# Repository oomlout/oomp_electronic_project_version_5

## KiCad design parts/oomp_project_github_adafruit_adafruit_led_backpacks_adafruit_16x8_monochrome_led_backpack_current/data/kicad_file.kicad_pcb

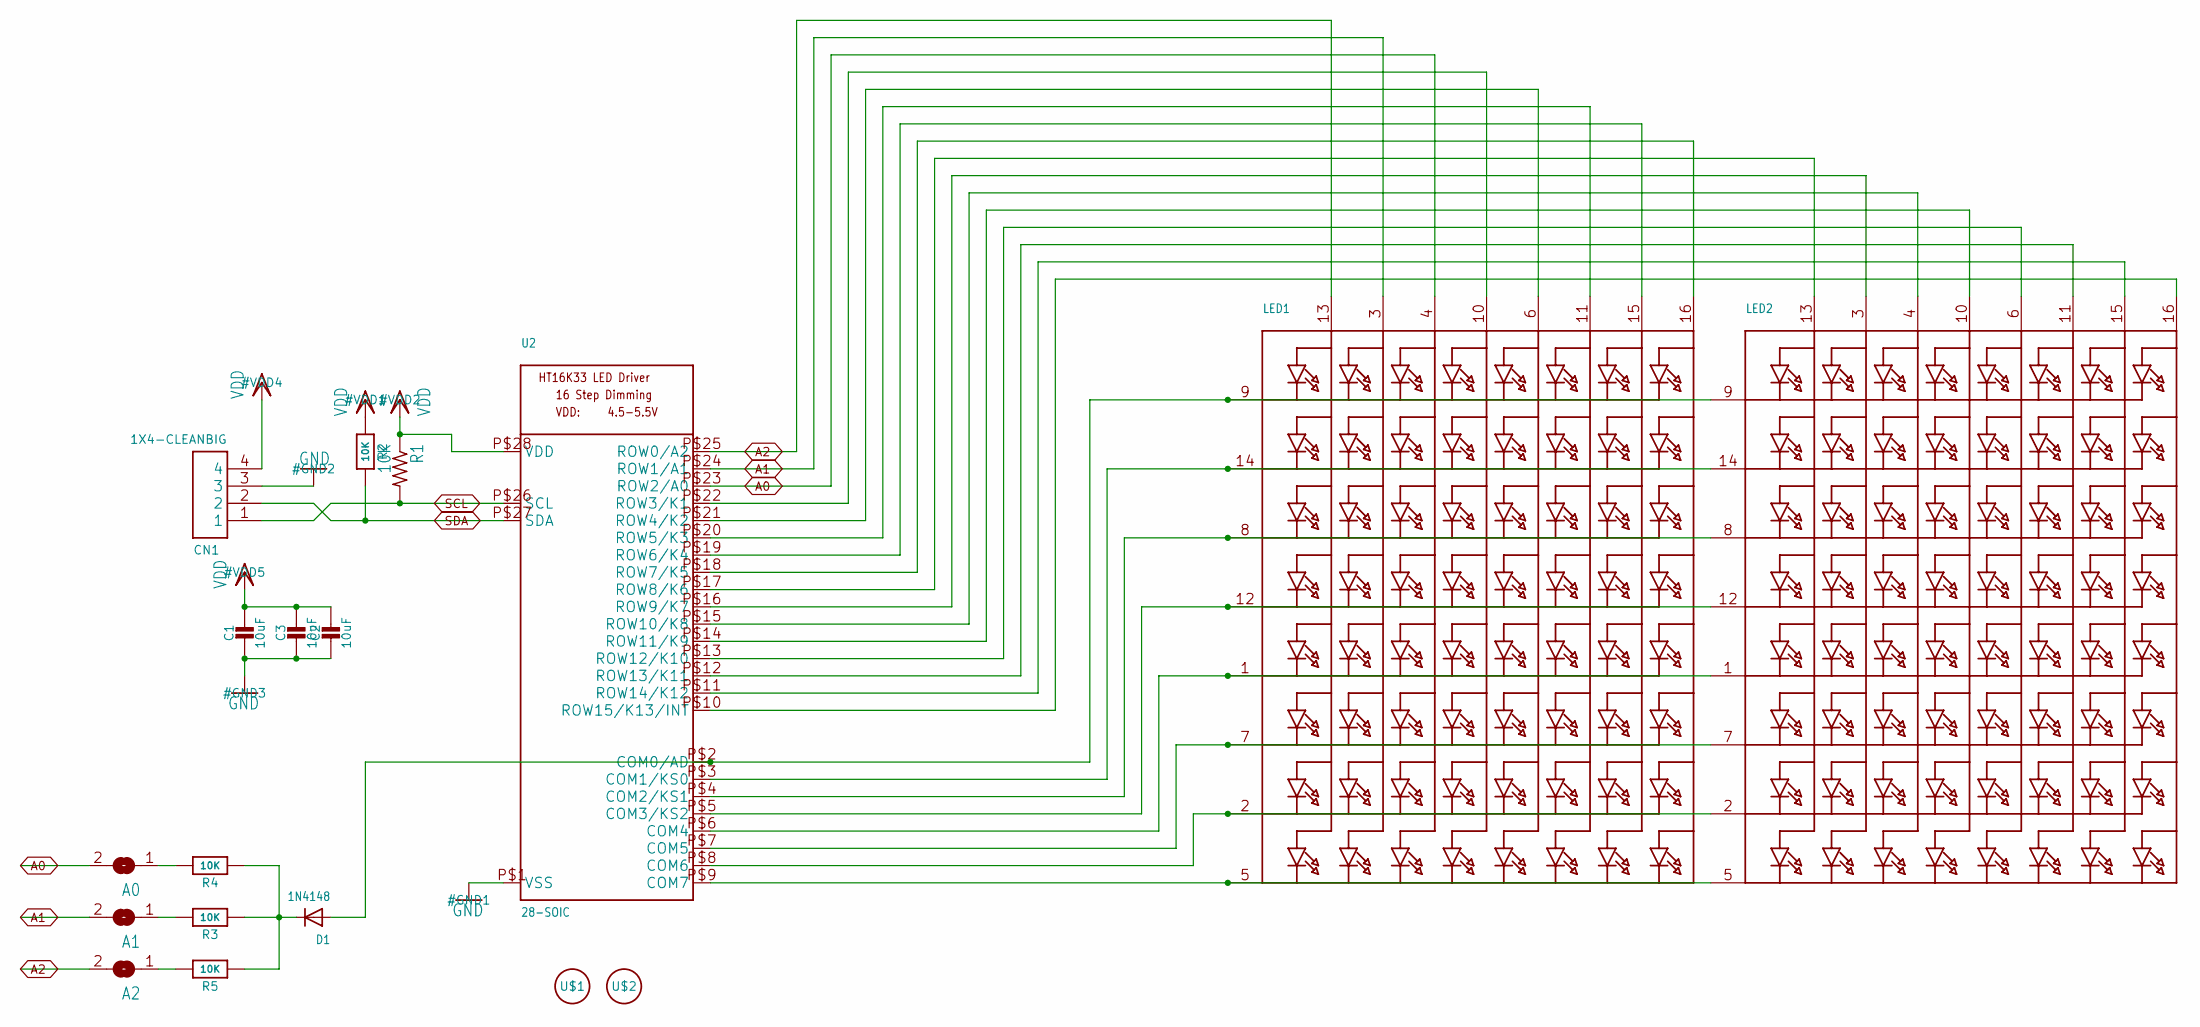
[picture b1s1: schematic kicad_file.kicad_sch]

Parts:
A0, A1, A2: SOLDERJUMPERREFLOW_NOPASTE; SOLDERJUMPER_REFLOW_NOPASTE
C1, C2, C3: 10uF; 0805-NO
CN1: 1X4-CLEANBIG; 1X04-CLEANBIG
D1: 1N4148; SOD-323F
LED1, LED2: DISP_SEGMENT_8X8_ROWCATHODEM12A881UR; SEGMENT_BL-M12A881UR
R1: 10K; R0805
R2, R3, R4, R5: 10K; 0805-NO
U2: 28-SOIC; SOP28_300MIL
U$1, U$2: FIDUCIAL; FIDUCIAL_1MM

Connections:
A0: A0.2, LED1.4 (A3), U2.P$23 (ROW2/A0)
A1: A1.2, LED1.3 (A2), U2.P$24 (ROW1/A1)
A2: A2.2, LED1.13 (A1), U2.P$25 (ROW0/A2)
GND: C1.2, C2.2, C3.2, CN1.3, U2.P$1 (VSS)
unnamed: LED1.5 (K8), LED2.5 (K8), U2.P$9 (COM7)
unnamed: LED1.2 (K7), LED2.2 (K7), U2.P$8 (COM6)
unnamed: LED1.7 (K6), LED2.7 (K6), U2.P$7 (COM5)
unnamed: LED1.1 (K5), LED2.1 (K5), U2.P$6 (COM4)
unnamed: LED1.12 (K4), LED2.12 (K4), U2.P$5 (COM3/KS2)
unnamed: LED1.8 (K3), LED2.8 (K3), U2.P$4 (COM2/KS1)
unnamed: LED1.14 (K2), LED2.14 (K2), U2.P$3 (COM1/KS0)
unnamed: D1.A, LED1.9 (K1), LED2.9 (K1), U2.P$2 (COM0/AD)
unnamed: A2.1, R5.2
unnamed: LED2.15 (A7), U2.P$11 (ROW14/K12)
unnamed: LED2.11 (A6), U2.P$12 (ROW13/K11)
unnamed: LED2.16 (A8), U2.P$10 (ROW15/K13/INT)
unnamed: D1.C, R3.1, R4.1, R5.1
unnamed: A1.1, R3.2
unnamed: A0.1, R4.2
unnamed: LED1.16 (A8), U2.P$18 (ROW7/K5)
unnamed: LED1.15 (A7), U2.P$19 (ROW6/K4)
unnamed: LED1.6 (A5), U2.P$21 (ROW4/K2)
unnamed: LED1.10 (A4), U2.P$22 (ROW3/K1)
unnamed: LED1.11 (A6), U2.P$20 (ROW5/K3)
unnamed: LED2.13 (A1), U2.P$17 (ROW8/K6)
unnamed: LED2.3 (A2), U2.P$16 (ROW9/K7)
unnamed: LED2.10 (A4), U2.P$14 (ROW11/K9)
unnamed: LED2.4 (A3), U2.P$15 (ROW10/K8)
unnamed: LED2.6 (A5), U2.P$13 (ROW12/K10)
SCL: CN1.1, R1.2, U2.P$26 (SCL)
SDA: CN1.2, R2.2, U2.P$27 (SDA)
VDD: C1.1, C2.1, C3.1, CN1.4, R1.1, R2.1, U2.P$28 (VDD)

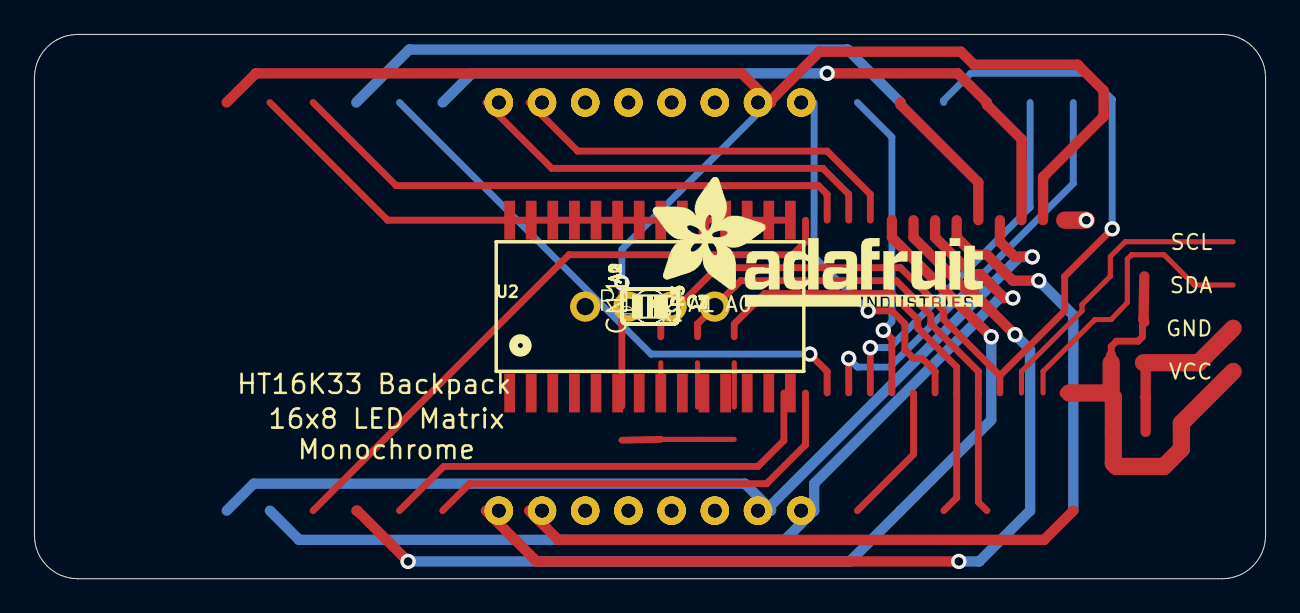
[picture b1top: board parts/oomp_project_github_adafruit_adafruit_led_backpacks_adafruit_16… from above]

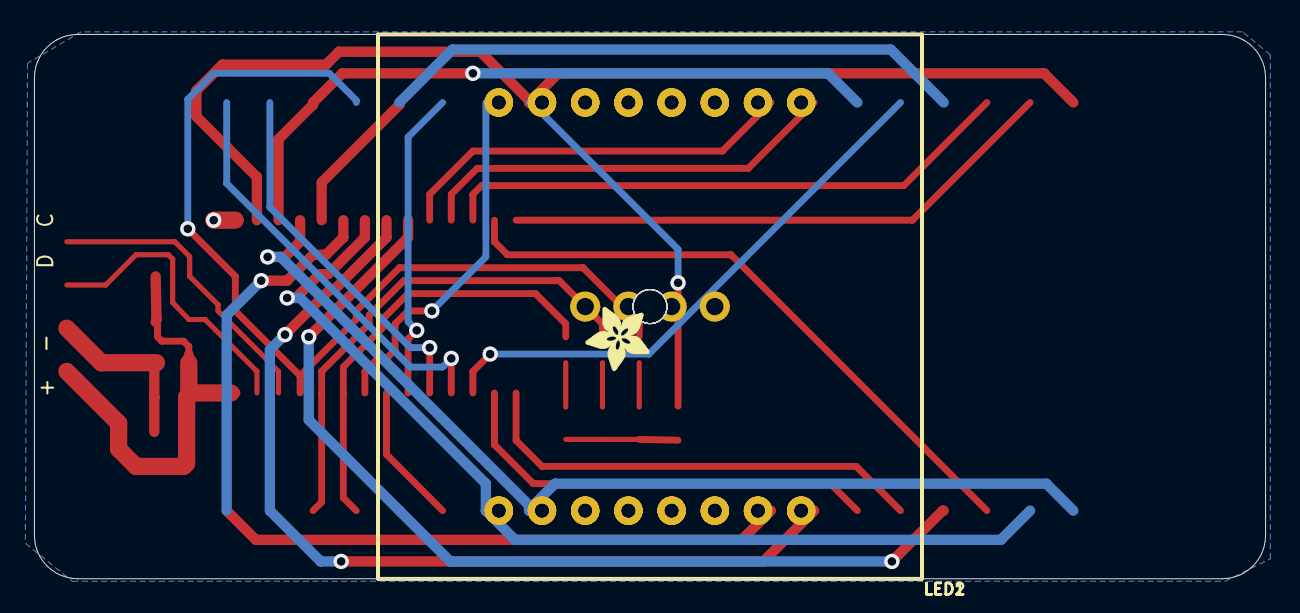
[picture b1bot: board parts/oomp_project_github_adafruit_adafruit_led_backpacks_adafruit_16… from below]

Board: 2 copper layers, 72.4 x 32.0 mm, 24 parts (3 on the bottom side), 32 nets.

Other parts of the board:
U$3: ADAFRUIT_TEXT_20MM
U$4: ADAFRUIT_3.5MM
UNK_HOLE_0: dummyfp0
UNK_HOLE_1: dummyfp1
UNK_HOLE_2: dummyfp2
UNK_HOLE_3: dummyfp3

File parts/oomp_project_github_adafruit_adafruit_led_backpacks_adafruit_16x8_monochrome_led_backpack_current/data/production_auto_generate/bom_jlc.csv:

Comment,Designator,Footprint,LCSC Part #
,U$4,Adafruit 16x8 Monochrome LED Backpack-import-fps:ADAFRUIT_3.5MM,
,U$3,Adafruit 16x8 Monochrome LED Backpack-import-fps:ADAFRUIT_TEXT_20MM,
,"LED1,LED2",Adafruit 16x8 Monochrome LED Backpack-import-fps:SEGMENT_BL-M12A881UR,
,"A0,A1,A2",Adafruit 16x8 Monochrome LED Backpack-import-fps:SOLDERJUMPER_REFLOW_NOPASTE,
10K,"R2,R3,R4,R5",Adafruit 16x8 Monochrome LED Backpack-import-fps:0805-NO,C17414
10K,R1,Adafruit 16x8 Monochrome LED Backpack-import-fps:R0805,C17414
10uF,"C1,C2,C3",Adafruit 16x8 Monochrome LED Backpack-import-fps:0805-NO,
1N4148,D1,Adafruit 16x8 Monochrome LED Backpack-import-fps:SOD-323F,
1X4-CLEANBIG,CN1,Adafruit 16x8 Monochrome LED Backpack-import-fps:1X04-CLEANBIG,
28-SOIC,U2,Adafruit 16x8 Monochrome LED Backpack-import-fps:SOP28_300MIL,
FIDUCIAL,"U$1,U$2",Adafruit 16x8 Monochrome LED Backpack-import-fps:FIDUCIAL_1MM,

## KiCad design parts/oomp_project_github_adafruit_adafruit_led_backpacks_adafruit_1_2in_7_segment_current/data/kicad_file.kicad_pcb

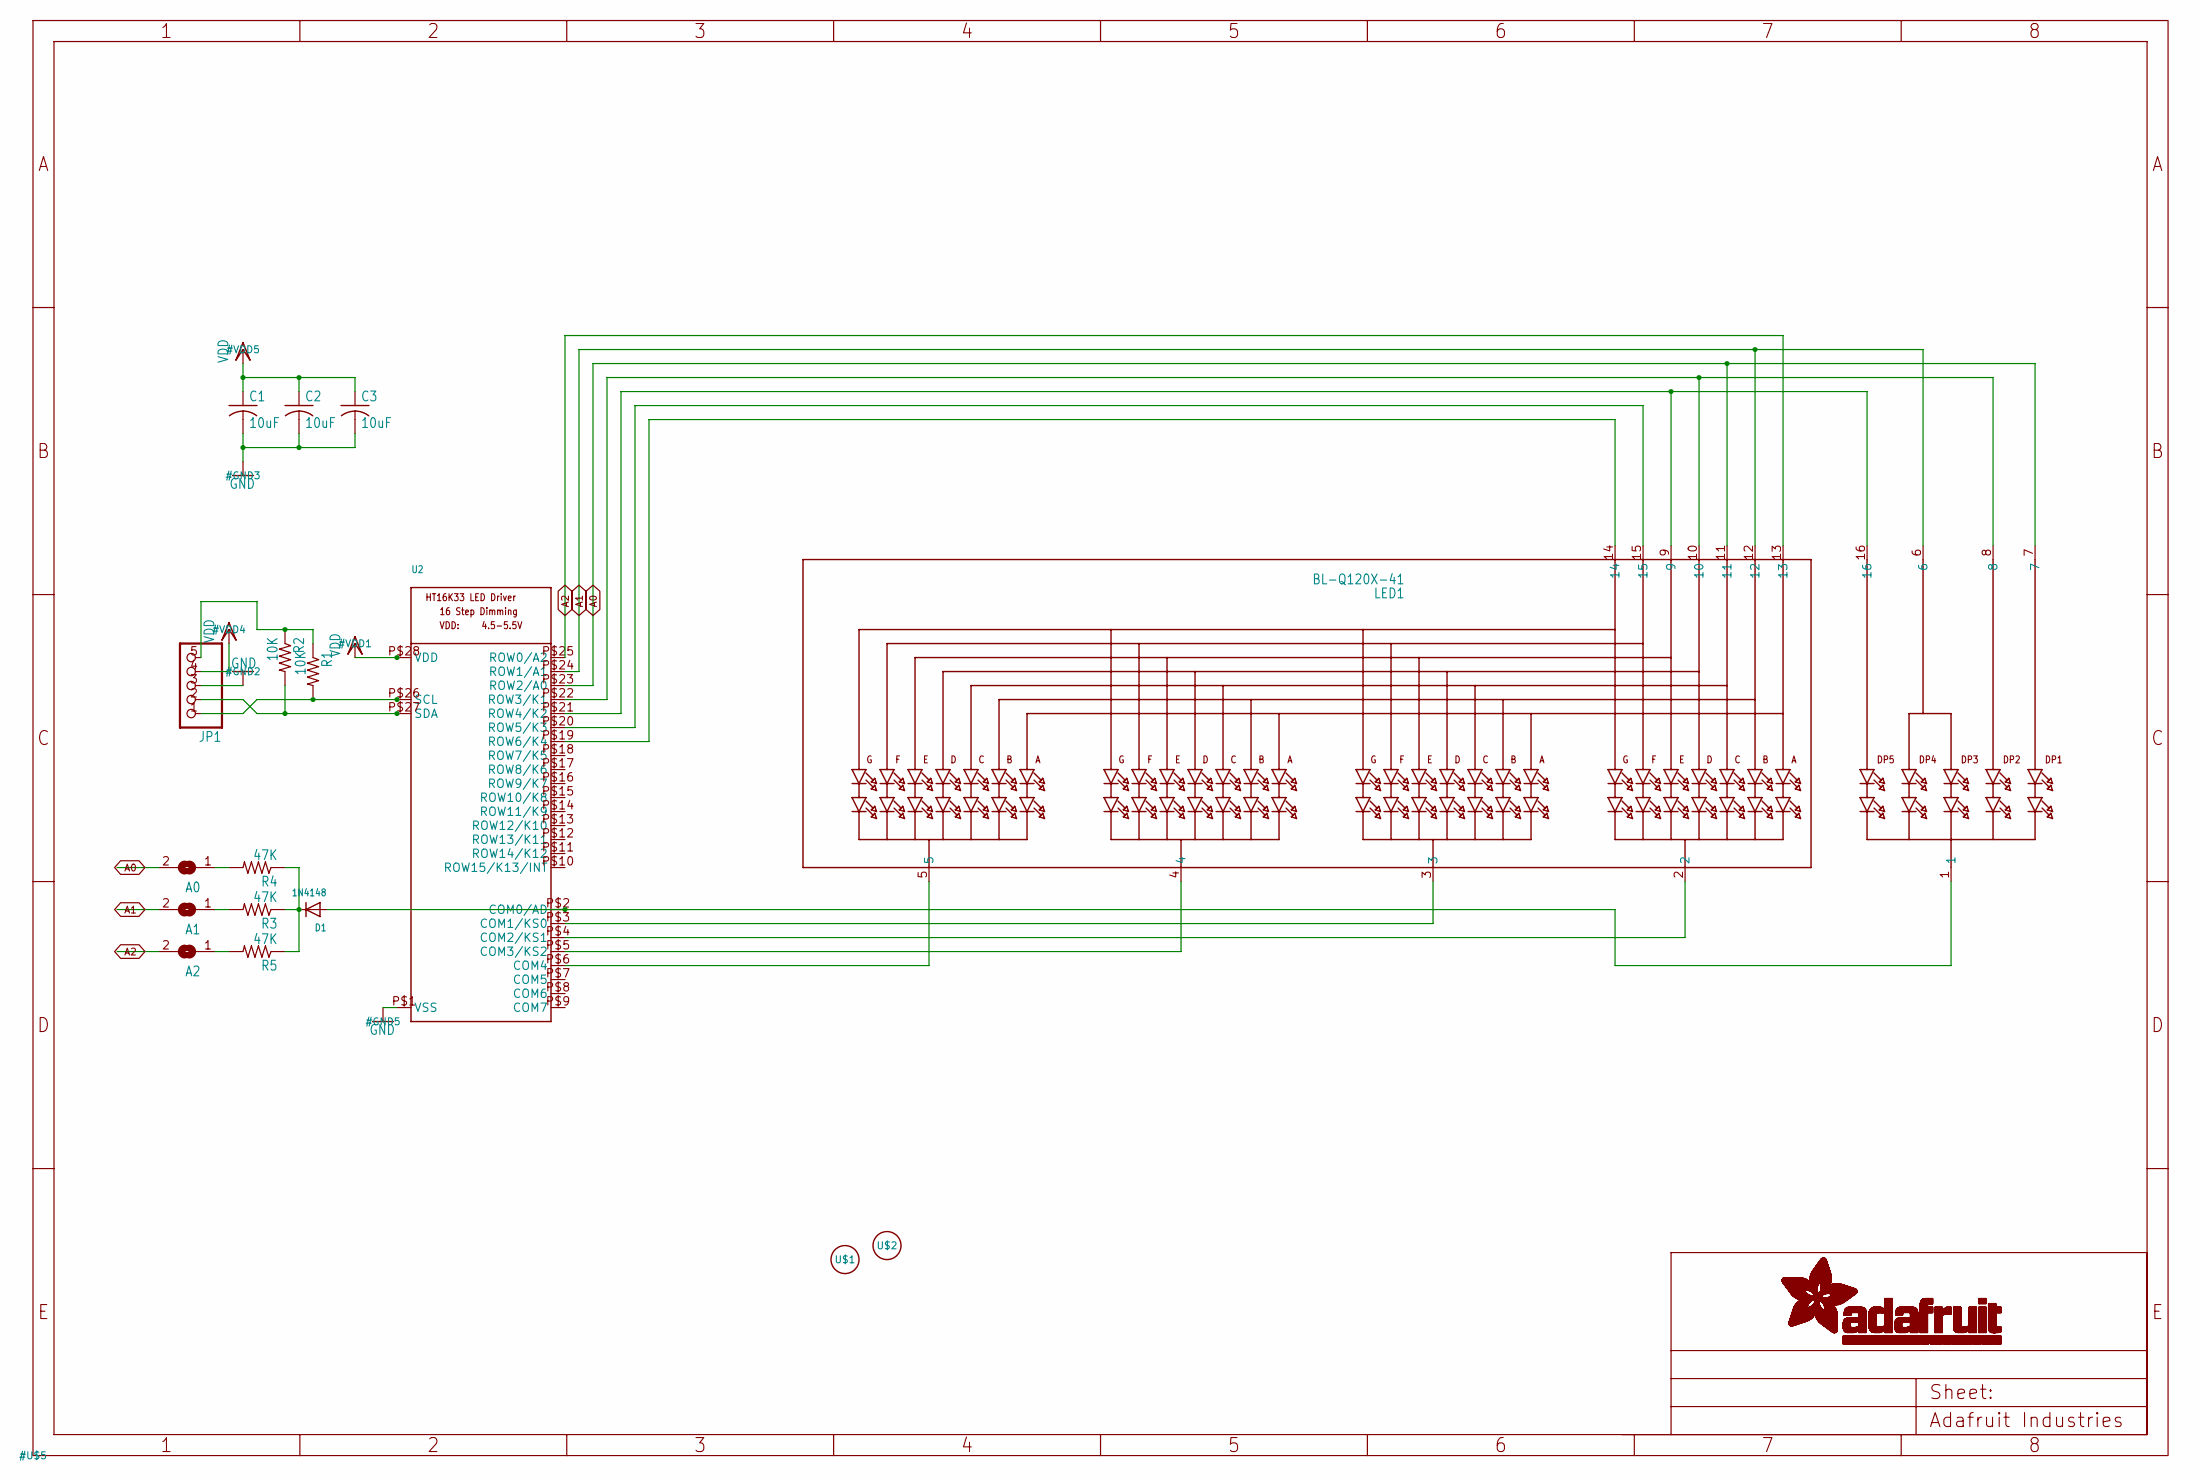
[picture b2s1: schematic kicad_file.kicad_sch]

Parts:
A0, A1, A2: SOLDERJUMPERREFLOW_NOPASTE; SOLDERJUMPER_REFLOW_NOPASTE
C1, C2, C3: 10uF; C0805K
D1: 1N4148; SOD-323F
JP1: HEADER-1X576MIL; 1X05_ROUND_76
LED1: BL-Q120X-41; SEGMENT_BL-Q120A
R1, R2: 10K; R0805
R3, R4, R5: 47K; R0805
U2: HT16K33_SOP28; SOP28_300MIL
U$1, U$2: FIDUCIAL; FIDUCIAL_1MM

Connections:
A0: A0.2, LED1.7, LED1.11, U2.P$23 (ROW2/A0)
A1: A1.2, LED1.6, LED1.12, U2.P$24 (ROW1/A1)
A2: A2.2, LED1.13, U2.P$25 (ROW0/A2)
GND: C1.2, C2.2, C3.2, JP1.3, U2.P$1 (VSS)
unnamed: D1.C, R3.1, R4.1, R5.1
unnamed: D1.A, LED1.1, U2.P$2 (COM0/AD)
unnamed: LED1.3, U2.P$3 (COM1/KS0)
unnamed: LED1.4, U2.P$5 (COM3/KS2)
unnamed: LED1.5, U2.P$6 (COM4)
unnamed: LED1.2, U2.P$4 (COM2/KS1)
unnamed: A2.1, R5.2
unnamed: JP1.5, R1.1, R2.1
unnamed: LED1.8, LED1.10, U2.P$22 (ROW3/K1)
unnamed: LED1.9, LED1.16, U2.P$21 (ROW4/K2)
unnamed: LED1.15, U2.P$20 (ROW5/K3)
unnamed: LED1.14, U2.P$19 (ROW6/K4)
unnamed: A1.1, R3.2
unnamed: A0.1, R4.2
SCL: JP1.1, R1.2, U2.P$26 (SCL)
SDA: JP1.2, R2.2, U2.P$27 (SDA)
VDD: C1.1, C2.1, C3.1, JP1.4, U2.P$28 (VDD)

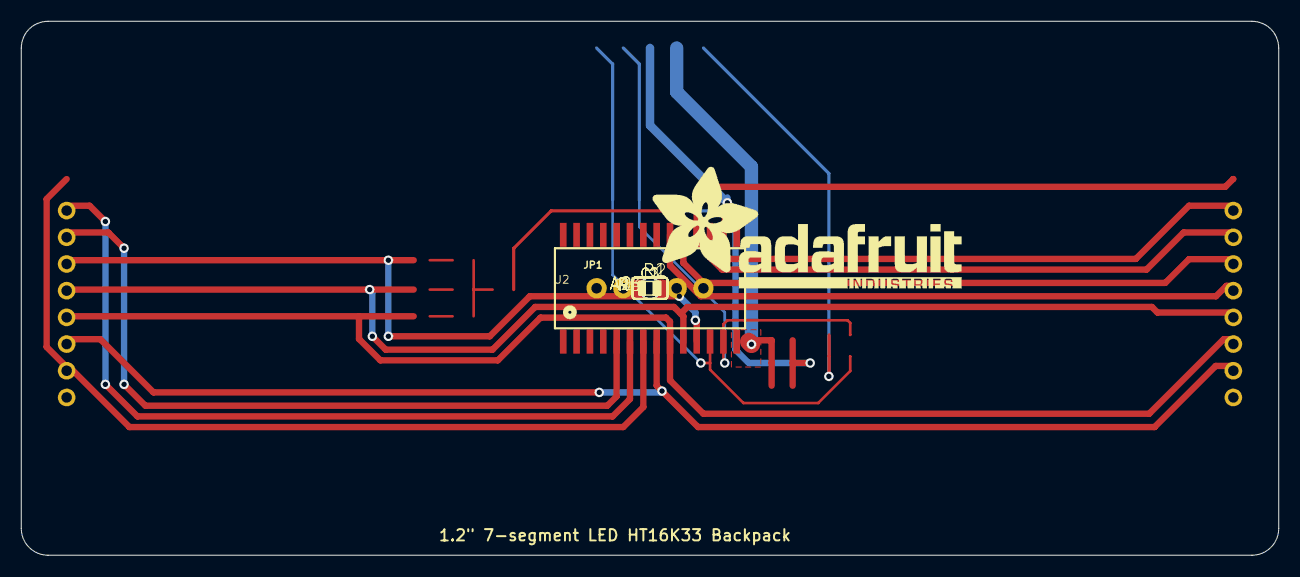
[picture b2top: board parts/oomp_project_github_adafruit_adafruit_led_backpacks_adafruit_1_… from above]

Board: 16 copper layers, 119.6 x 50.8 mm, 22 parts (1 on the bottom side), 21 nets.

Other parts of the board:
U$3: ADAFRUIT_TEXT_30MM
UNK_HOLE_0: dummyfp0
UNK_HOLE_1: dummyfp1
UNK_HOLE_2: dummyfp2
UNK_HOLE_3: dummyfp3

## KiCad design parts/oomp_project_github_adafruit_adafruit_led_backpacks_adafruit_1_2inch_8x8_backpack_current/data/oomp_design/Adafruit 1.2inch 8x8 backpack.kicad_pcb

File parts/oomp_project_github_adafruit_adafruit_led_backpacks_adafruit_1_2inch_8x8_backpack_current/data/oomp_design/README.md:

# OOMP KiCad design copy

Open `Adafruit 1.2inch 8x8 backpack.kicad_pro` (or the `.kicad_pcb` / `.kicad_sch`) in KiCad. Local OOMP libraries are under `libraries/`. Original inputs are preserved in [../original/](../original/).

Only verified unchanged installed KiCad defaults were renamed. Modified, custom, unmatched and unavailable items remain unchanged. Soldering variants are never swapped during conversion. Existing pad coordinates, nets and UUIDs are preserved.

See [conversion_report.yaml](conversion_report.yaml) for every conversion and skip. Copy this directory before editing; regeneration refuses to overwrite edited design files.

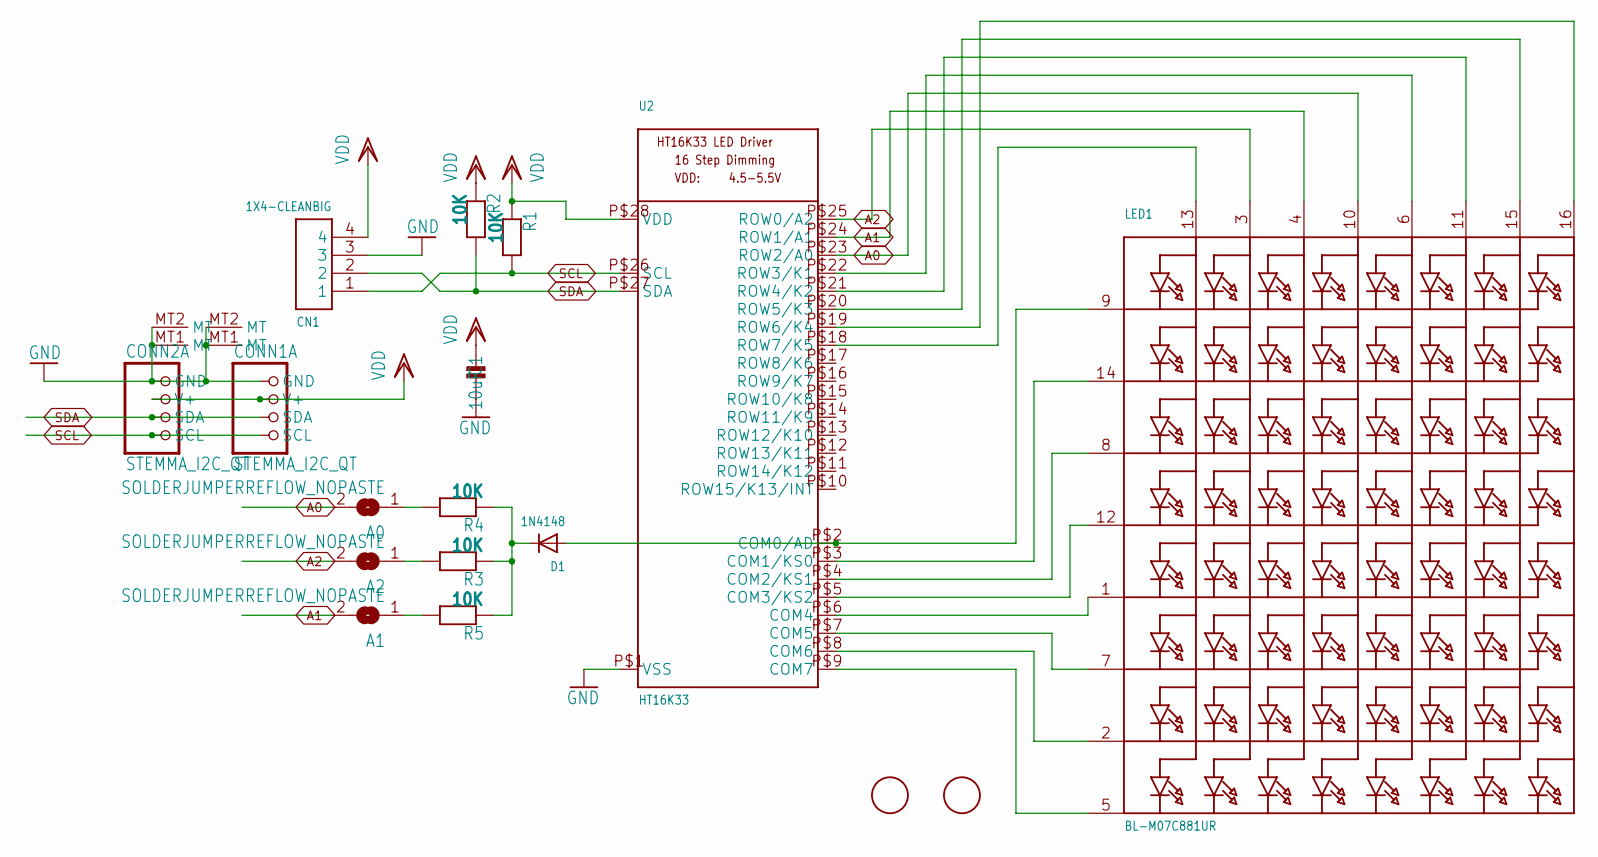
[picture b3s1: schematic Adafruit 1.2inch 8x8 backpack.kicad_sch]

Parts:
A0, A1, A2: SOLDERJUMPERREFLOW_NOPASTE; SOLDERJUMPER_REFLOW_NOPASTE
C1: 10uF; 0805-NO
CN1: 1X4-CLEANBIG; 1X04-CLEANBIG
CONN1, CONN2: STEMMA_I2C_QT; JST_SH4; LCSC C2845363
D1: 1N4148; SOD-323
LED1: BL-M07C881UR; SEGMENT_BL-M12A881UR
R1, R2, R3, R4, R5: 10K; 0603-NO
U2: HT16K33; SOP28_300MIL
U$1, U$2: FIDUCIAL; FIDUCIAL_1MM

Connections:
A0: A0.2, LED1.10 (A4), U2.P$23 (ROW2/A0)
A1: A1.2, LED1.4 (A3), U2.P$24 (ROW1/A1)
A2: A2.2, LED1.3 (A2), U2.P$25 (ROW0/A2)
GND: C1.2, CN1.3, CONN1.1 (GND), CONN1.MT1 (MT), CONN1.MT2 (MT), CONN2.1 (GND), CONN2.MT1 (MT), CONN2.MT2 (MT), U2.P$1 (VSS)
unnamed: LED1.5 (K8), U2.P$9 (COM7)
unnamed: LED1.2 (K7), U2.P$8 (COM6)
unnamed: LED1.7 (K6), U2.P$7 (COM5)
unnamed: LED1.1 (K5), U2.P$6 (COM4)
unnamed: LED1.12 (K4), U2.P$5 (COM3/KS2)
unnamed: LED1.8 (K3), U2.P$4 (COM2/KS1)
unnamed: LED1.14 (K2), U2.P$3 (COM1/KS0)
unnamed: D1.A, LED1.9 (K1), U2.P$2 (COM0/AD)
unnamed: A1.1, R5.2
unnamed: LED1.6 (A5), U2.P$22 (ROW3/K1)
unnamed: LED1.11 (A6), U2.P$21 (ROW4/K2)
unnamed: D1.C, R3.1, R4.1, R5.1
unnamed: LED1.13 (A1), U2.P$18 (ROW7/K5)
unnamed: A2.1, R3.2
unnamed: A0.1, R4.2
SCL: CN1.1, CONN1.4 (SCL), CONN2.4 (SCL), R1.2, U2.P$26 (SCL)
SDA: CN1.2, CONN1.3 (SDA), CONN2.3 (SDA), R2.2, U2.P$27 (SDA)
SEG_F: LED1.15 (A7), U2.P$20 (ROW5/K3)
SEG_G: LED1.16 (A8), U2.P$19 (ROW6/K4)
VDD: C1.1, CN1.4, CONN1.2 (V+), CONN2.2 (V+), R1.1, R2.1, U2.P$28 (VDD)

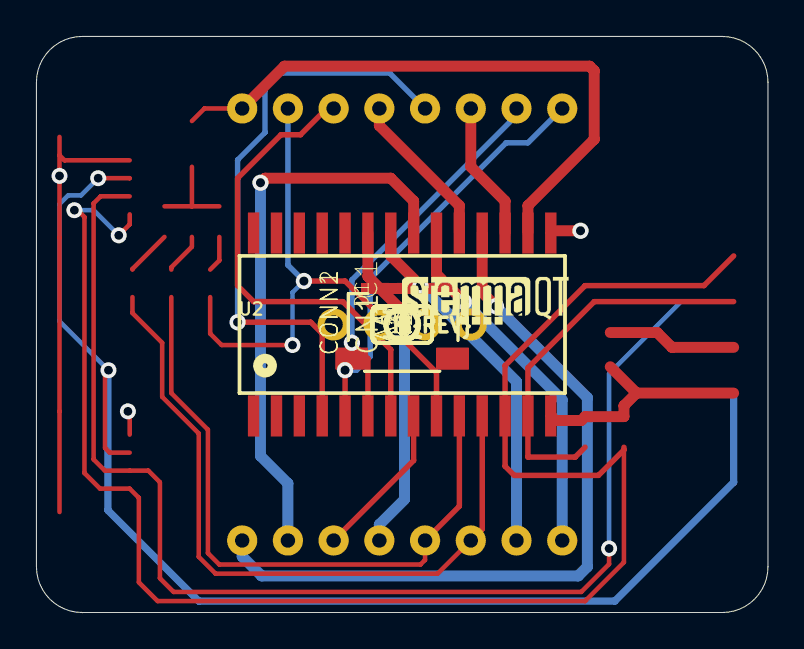
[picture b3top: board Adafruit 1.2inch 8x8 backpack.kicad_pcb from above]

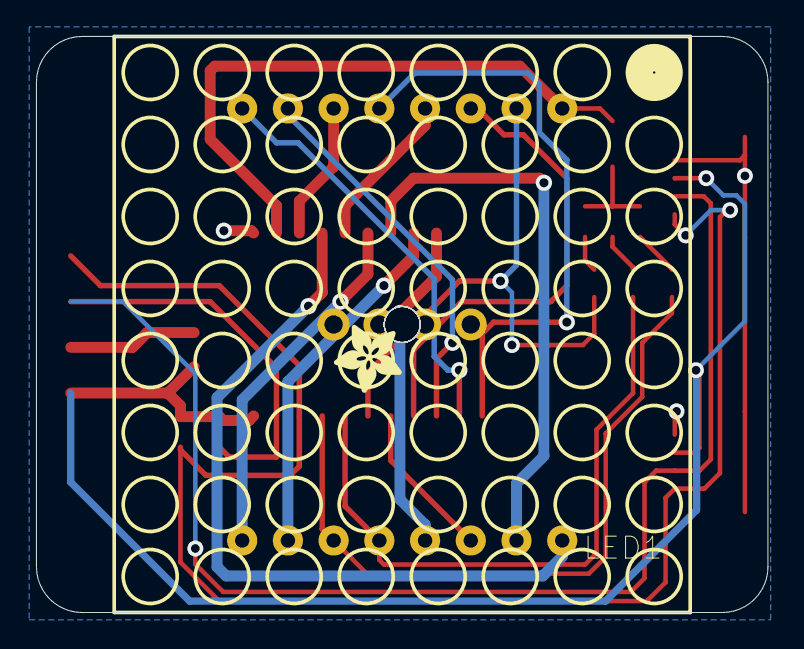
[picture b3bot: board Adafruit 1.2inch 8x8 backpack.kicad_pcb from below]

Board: 16 copper layers, 40.6 x 32.0 mm, 38 parts (6 on the bottom side), 24 nets.

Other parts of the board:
PLABEL0: PLABEL0
PLABEL1: PLABEL1
PLABEL2: PLABEL2
PLABEL3: PLABEL3
PLABEL4: PLABEL4
PLABEL5: PLABEL5
PLABEL6: PLABEL6
PLABEL7: PLABEL7
PLABEL8: PLABEL8
PLABEL9: PLABEL9
PLABEL10: PLABEL10
PLABEL11: PLABEL11
PLABEL12: PLABEL12
PLABEL13: PLABEL13
U$3: ADAFRUIT_3.5MM
U$4: PCBFEAT-REV-040
U$5: STEMMAQT
UNK_HOLE_0: dummyfp0
UNK_HOLE_1: dummyfp1
UNK_HOLE_2: dummyfp2
UNK_HOLE_3: dummyfp3

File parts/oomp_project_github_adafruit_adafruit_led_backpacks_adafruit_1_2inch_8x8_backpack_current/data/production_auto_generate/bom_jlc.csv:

Comment,Designator,Footprint,LCSC Part #
,U$3,Adafruit 1.2inch 8x8 backpack-import-fps:ADAFRUIT_3.5MM,
,U$4,Adafruit 1.2inch 8x8 backpack-import-fps:PCBFEAT-REV-040,
,PLABEL0,Adafruit 1.2inch 8x8 backpack-import-fps:PLABEL0,
,PLABEL1,Adafruit 1.2inch 8x8 backpack-import-fps:PLABEL1,
,PLABEL10,Adafruit 1.2inch 8x8 backpack-import-fps:PLABEL10,
,PLABEL11,Adafruit 1.2inch 8x8 backpack-import-fps:PLABEL11,
,PLABEL12,Adafruit 1.2inch 8x8 backpack-import-fps:PLABEL12,
,PLABEL13,Adafruit 1.2inch 8x8 backpack-import-fps:PLABEL13,
,PLABEL2,Adafruit 1.2inch 8x8 backpack-import-fps:PLABEL2,
,PLABEL3,Adafruit 1.2inch 8x8 backpack-import-fps:PLABEL3,
,PLABEL4,Adafruit 1.2inch 8x8 backpack-import-fps:PLABEL4,
,PLABEL5,Adafruit 1.2inch 8x8 backpack-import-fps:PLABEL5,
,PLABEL6,Adafruit 1.2inch 8x8 backpack-import-fps:PLABEL6,
,PLABEL7,Adafruit 1.2inch 8x8 backpack-import-fps:PLABEL7,
,PLABEL8,Adafruit 1.2inch 8x8 backpack-import-fps:PLABEL8,
,PLABEL9,Adafruit 1.2inch 8x8 backpack-import-fps:PLABEL9,
,"A0,A1,A2",Adafruit 1.2inch 8x8 backpack-import-fps:SOLDERJUMPER_REFLOW_NOPASTE,
,U$5,Adafruit 1.2inch 8x8 backpack-import-fps:STEMMAQT,
10K,"R1,R2,R3,R4,R5",Adafruit 1.2inch 8x8 backpack-import-fps:0603-NO,C98220
10uF,C1,Adafruit 1.2inch 8x8 backpack-import-fps:0805-NO,
1N4148,D1,Adafruit 1.2inch 8x8 backpack-import-fps:SOD-323,
1X4-CLEANBIG,CN1,Adafruit 1.2inch 8x8 backpack-import-fps:1X04-CLEANBIG,
BL-M07C881UR,LED1,Adafruit 1.2inch 8x8 backpack-import-fps:SEGMENT_BL-M12A881UR,
FIDUCIAL,"U$1,U$2",Adafruit 1.2inch 8x8 backpack-import-fps:FIDUCIAL_1MM,
HT16K33,U2,Adafruit 1.2inch 8x8 backpack-import-fps:SOP28_300MIL,
STEMMA_I2C_QT,"CONN1,CONN2",Adafruit 1.2inch 8x8 backpack-import-fps:JST_SH4,C160404

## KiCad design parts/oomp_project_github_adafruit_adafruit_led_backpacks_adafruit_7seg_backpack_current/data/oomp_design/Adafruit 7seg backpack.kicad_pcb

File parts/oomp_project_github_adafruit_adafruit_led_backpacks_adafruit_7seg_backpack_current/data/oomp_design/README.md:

# OOMP KiCad design copy

Open `Adafruit 7seg backpack.kicad_pro` (or the `.kicad_pcb` / `.kicad_sch`) in KiCad. Local OOMP libraries are under `libraries/`. Original inputs are preserved in [../original/](../original/).

Only verified unchanged installed KiCad defaults were renamed. Modified, custom, unmatched and unavailable items remain unchanged. Soldering variants are never swapped during conversion. Existing pad coordinates, nets and UUIDs are preserved.

See [conversion_report.yaml](conversion_report.yaml) for every conversion and skip. Copy this directory before editing; regeneration refuses to overwrite edited design files.

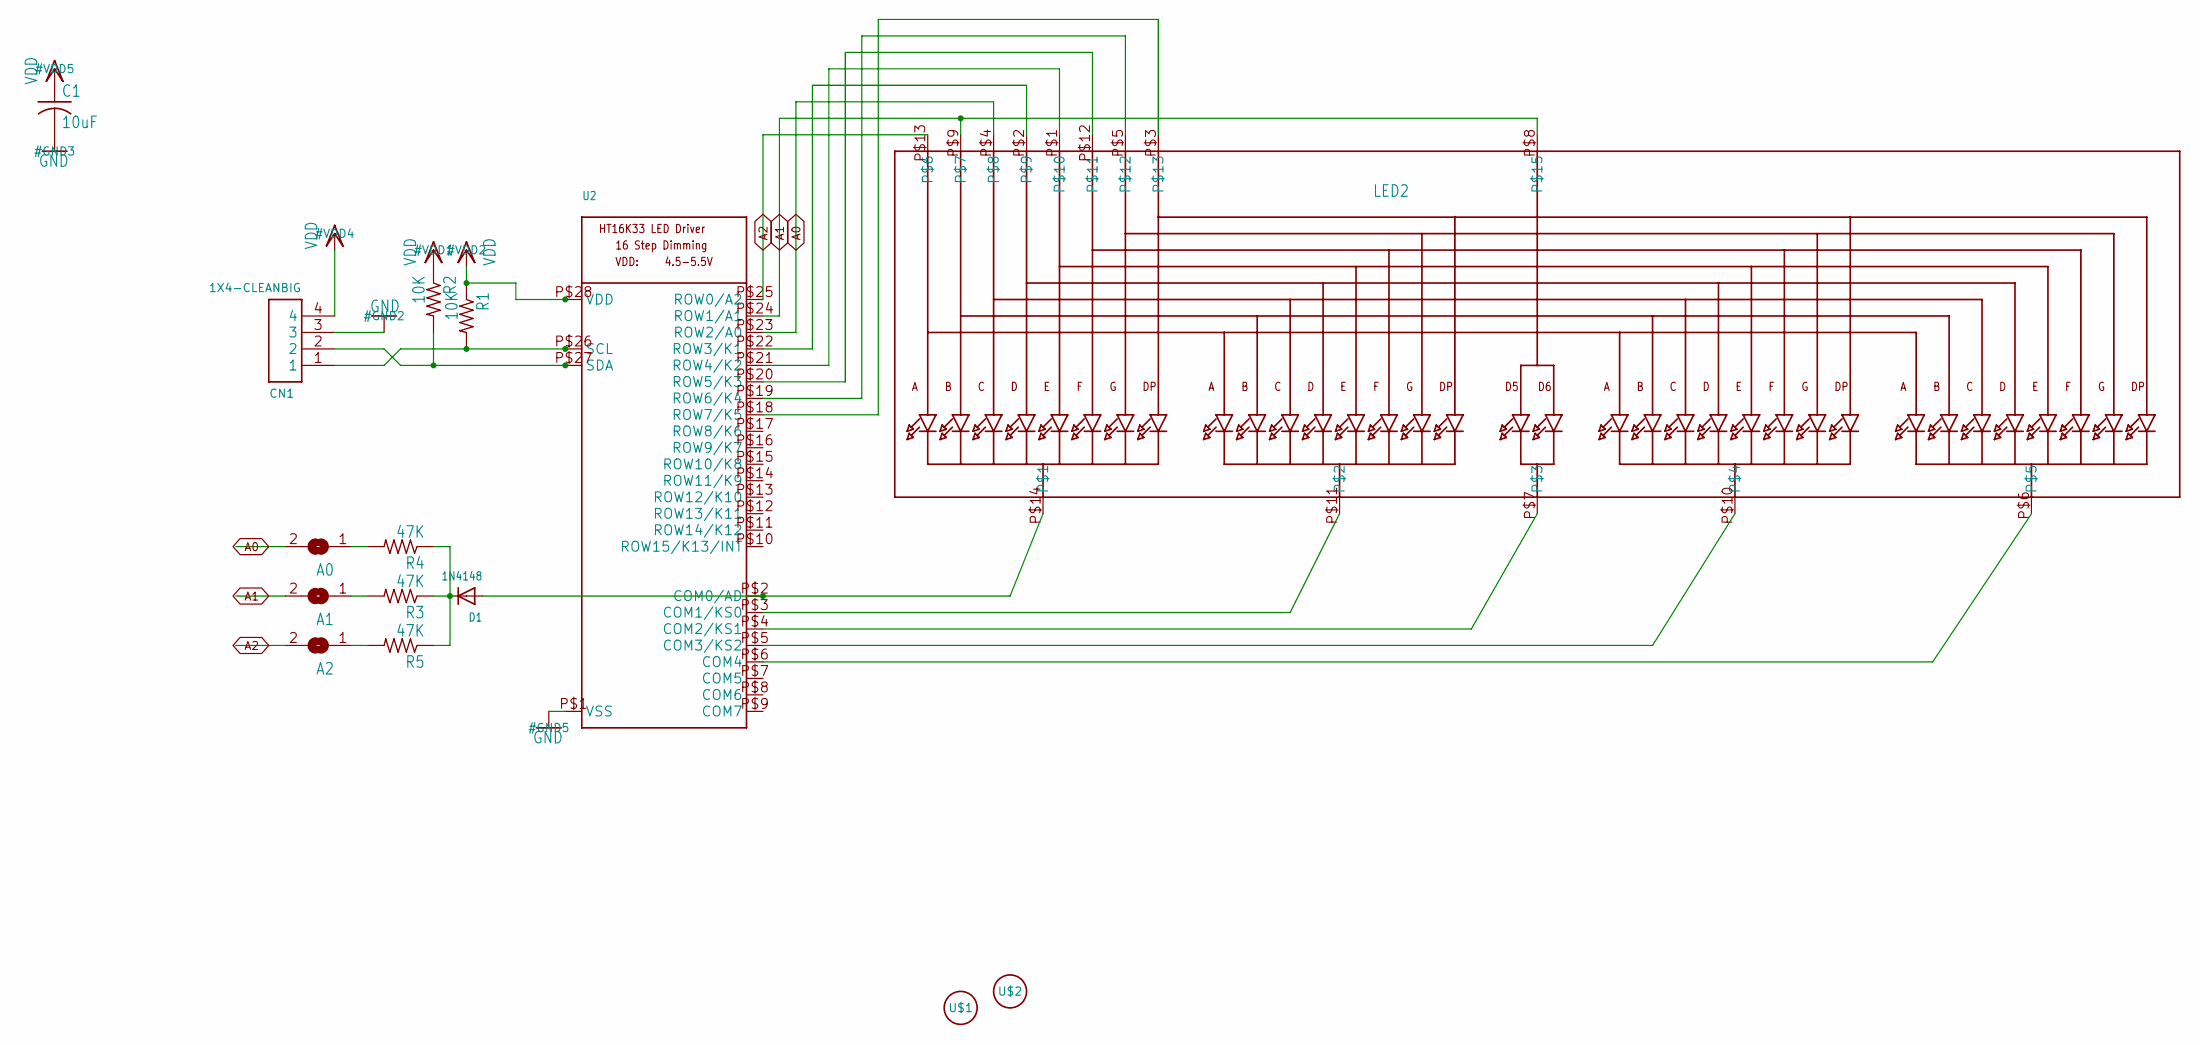
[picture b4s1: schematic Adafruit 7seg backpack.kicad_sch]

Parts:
A0, A1, A2: SOLDERJUMPERREFLOW_NOPASTE; SOLDERJUMPER_REFLOW_NOPASTE
C1: 10uF; C0805K
CN1: 1X4-CLEANBIG; 1X04-CLEANBIG
D1: 1N4148; SOD-323F
LED2: DISP_SEGMENT_4DIGIT_BL-Q56C43; SEGMENT-BL-Q56C43
R1, R2: 10K; R0805
R3, R4, R5: 47K; R0805
U2: HT16K33_SOP28; SOP28_300MIL
U$1, U$2: FIDUCIAL; FIDUCIAL_1MM

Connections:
A0: A0.2, LED2.P$4, U2.P$23 (ROW2/A0)
A1: A1.2, LED2.P$8, LED2.P$9, U2.P$24 (ROW1/A1)
A2: A2.2, LED2.P$13, U2.P$25 (ROW0/A2)
GND: C1.2, CN1.3, U2.P$1 (VSS)
unnamed: D1.C, R3.1, R4.1, R5.1
unnamed: D1.A, LED2.P$14, U2.P$2 (COM0/AD)
unnamed: LED2.P$11, U2.P$3 (COM1/KS0)
unnamed: LED2.P$7, U2.P$4 (COM2/KS1)
unnamed: LED2.P$10, U2.P$5 (COM3/KS2)
unnamed: LED2.P$6, U2.P$6 (COM4)
unnamed: A2.1, R5.2
unnamed: LED2.P$2, U2.P$22 (ROW3/K1)
unnamed: LED2.P$1, U2.P$21 (ROW4/K2)
unnamed: LED2.P$12, U2.P$20 (ROW5/K3)
unnamed: LED2.P$5, U2.P$19 (ROW6/K4)
unnamed: LED2.P$3, U2.P$18 (ROW7/K5)
unnamed: A1.1, R3.2
unnamed: A0.1, R4.2
SCL: CN1.1, R1.2, U2.P$26 (SCL)
SDA: CN1.2, R2.2, U2.P$27 (SDA)
VDD: C1.1, CN1.4, R1.1, R2.1, U2.P$28 (VDD)

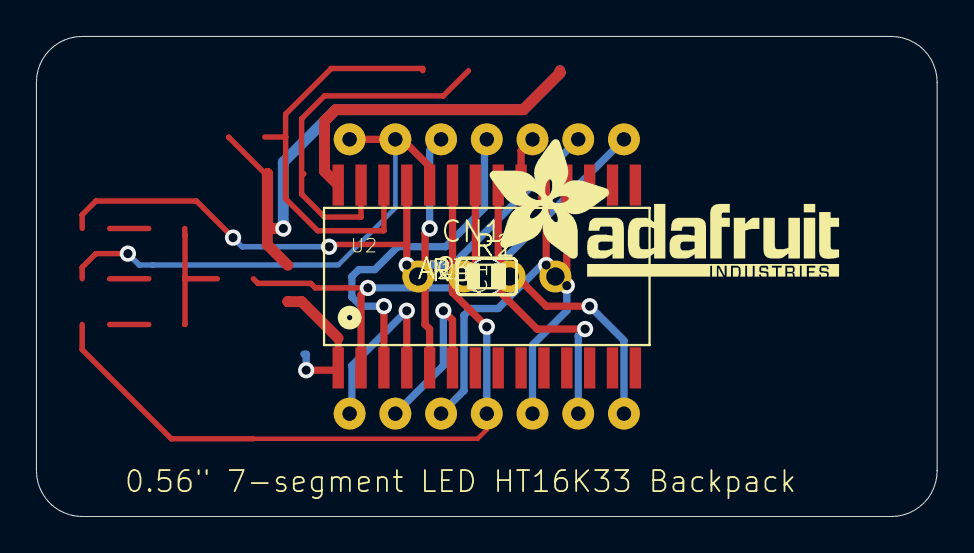
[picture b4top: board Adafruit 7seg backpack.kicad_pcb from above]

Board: 16 copper layers, 50.0 x 26.7 mm, 20 parts (1 on the bottom side), 21 nets.

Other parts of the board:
U$3: ADAFRUIT_TEXT_20MM
UNK_HOLE_0: dummyfp0
UNK_HOLE_1: dummyfp1
UNK_HOLE_2: dummyfp2
UNK_HOLE_3: dummyfp3

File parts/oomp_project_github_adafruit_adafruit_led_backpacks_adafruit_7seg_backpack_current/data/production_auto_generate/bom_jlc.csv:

Comment,Designator,Footprint,LCSC Part #
,U$3,Adafruit 7seg backpack-import-fps:ADAFRUIT_TEXT_20MM,
,"A0,A1,A2",Adafruit 7seg backpack-import-fps:SOLDERJUMPER_REFLOW_NOPASTE,
,U2,Adafruit 7seg backpack-import-fps:SOP28_300MIL,
10K,"R1,R2",Adafruit 7seg backpack-import-fps:R0805,C17414
10uF,C1,Adafruit 7seg backpack-import-fps:C0805K,
1N4148,D1,Adafruit 7seg backpack-import-fps:SOD-323F,
1X4-CLEANBIG,CN1,Adafruit 7seg backpack-import-fps:1X04-CLEANBIG,
47K,"R3,R4,R5",Adafruit 7seg backpack-import-fps:R0805,C17713
FIDUCIAL,"U$1,U$2",Adafruit 7seg backpack-import-fps:FIDUCIAL_1MM,
